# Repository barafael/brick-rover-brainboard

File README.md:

# brick-rover-brainboard
A PCB module with stm32f411 "Black Pill" and hc-12 that can serve as basic hobby RC-like sender or receiver.

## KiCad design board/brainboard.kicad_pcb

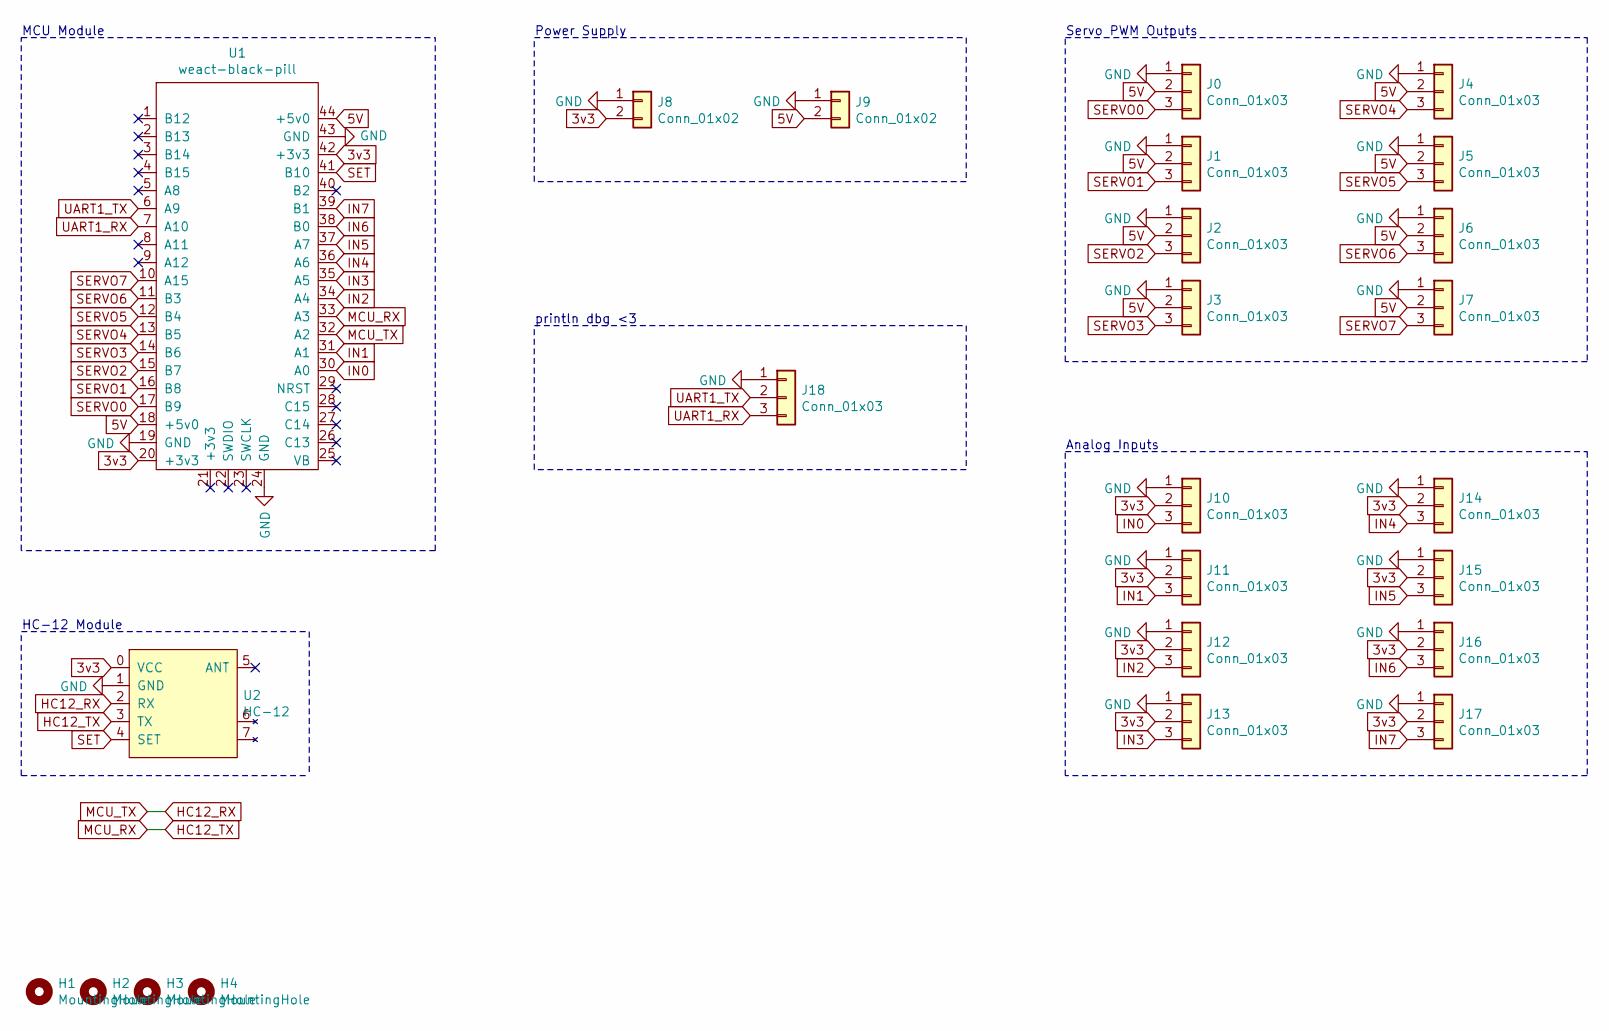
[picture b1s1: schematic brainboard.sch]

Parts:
H1: MountingHole; weact-blackpill-nodebug
H2, H3, H4: MountingHole; MountingHole_3.2mm_M3
J0, J1, J2, J3, J4, J5, J6, J7, J10, J11, J12, J13, J14, J15, J16, J17: Conn_01x03; PinHeader_1x03_P2.54mm_Vertical
J8, J9: Conn_01x02; PinHeader_1x02_P2.54mm_Vertical
J18: Conn_01x03; PinSocket_1x03_P2.54mm_Vertical
U1: weact-black-pill; weact-blackpill
U2: HC-12; hc12-module

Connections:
3v3: J8.2, J10.2, J11.2, J12.2, J13.2, J14.2, J15.2, J16.2, J17.2, U1.20 (+3v3), U1.42 (+3v3), U2.0 (VCC)
5V: J0.2, J1.2, J2.2, J3.2, J4.2, J5.2, J6.2, J7.2, J9.2, U1.18 (+5v0), U1.44 (+5v0)
GND: J0.1, J1.1, J2.1, J3.1, J4.1, J5.1, J6.1, J7.1, J8.1, J9.1, J10.1, J11.1, J12.1, J13.1, J14.1, J15.1, J16.1, J17.1, J18.1, U1.19 (GND), U1.24 (GND), U1.43 (GND), U2.1 (GND)
HC12_RX: U1.32 (A2), U2.2 (RX)
HC12_TX: U1.33 (A3), U2.3 (TX)
IN0: J10.3, U1.30 (A0)
IN1: J11.3, U1.31 (A1)
IN2: J12.3, U1.34 (A4)
IN3: J13.3, U1.35 (A5)
IN4: J14.3, U1.36 (A6)
IN5: J15.3, U1.37 (A7)
IN6: J16.3, U1.38 (B0)
IN7: J17.3, U1.39 (B1)
SERVO0: J0.3, U1.17 (B9)
SERVO1: J1.3, U1.16 (B8)
SERVO2: J2.3, U1.15 (B7)
SERVO3: J3.3, U1.14 (B6)
SERVO4: J4.3, U1.13 (B5)
SERVO5: J5.3, U1.12 (B4)
SERVO6: J6.3, U1.11 (B3)
SERVO7: J7.3, U1.10 (A15)
SET: U1.41 (B10), U2.4 (SET)
UART1_RX: J18.3, U1.7 (A10)
UART1_TX: J18.2, U1.6 (A9)

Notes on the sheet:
Analog Inputs
HC-12 Module
MCU Module
Servo PWM Outputs
Power Supply
println dbg <3

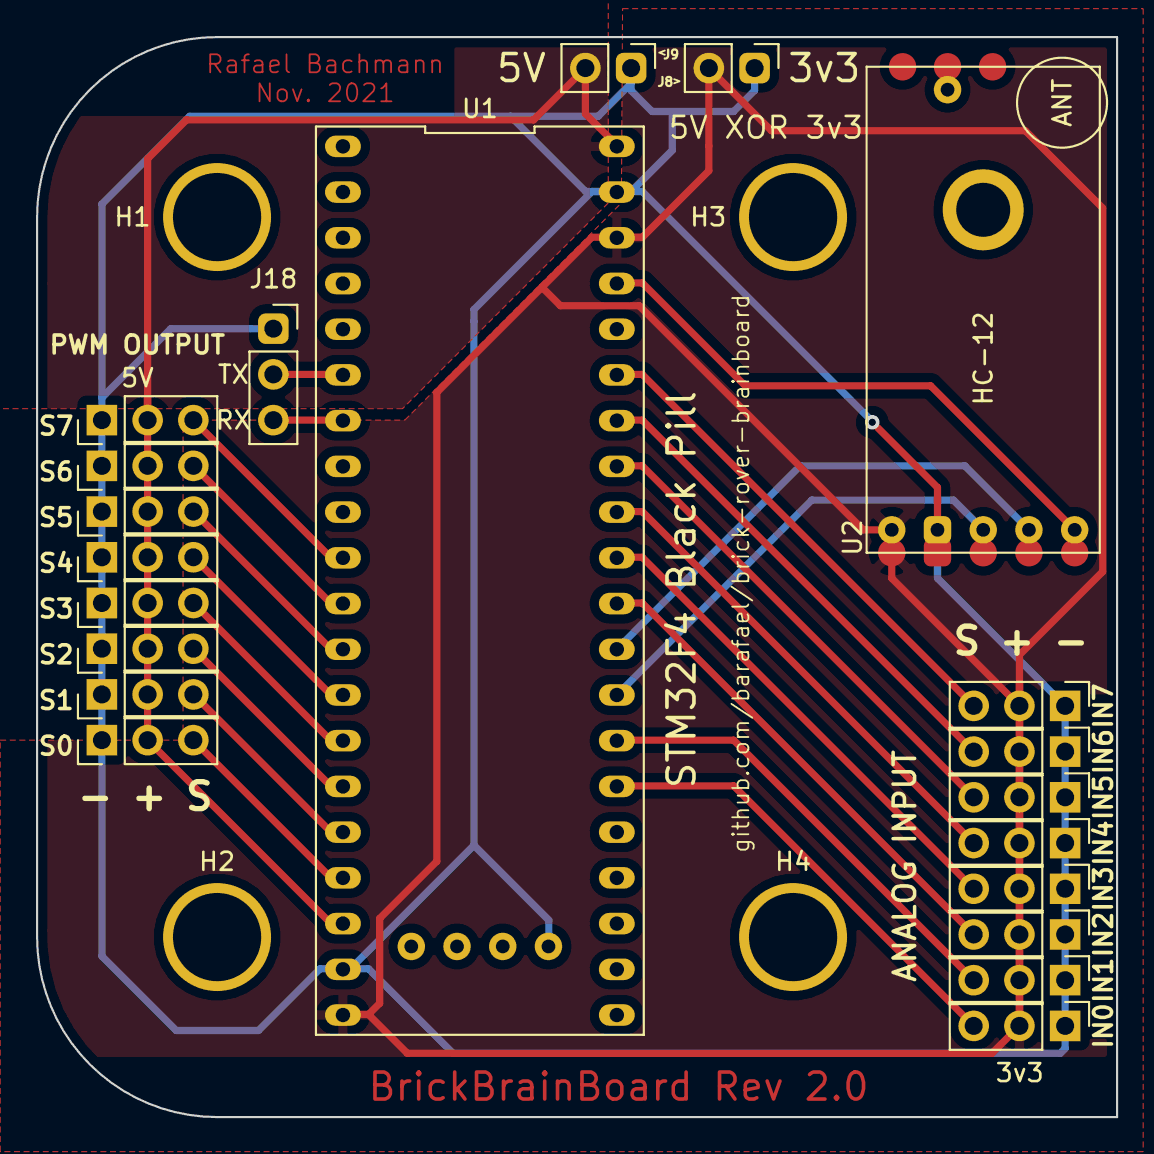
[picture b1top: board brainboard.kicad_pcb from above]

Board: 2 copper layers, 60.0 x 60.0 mm, 25 parts (0 on the bottom side), 24 nets.

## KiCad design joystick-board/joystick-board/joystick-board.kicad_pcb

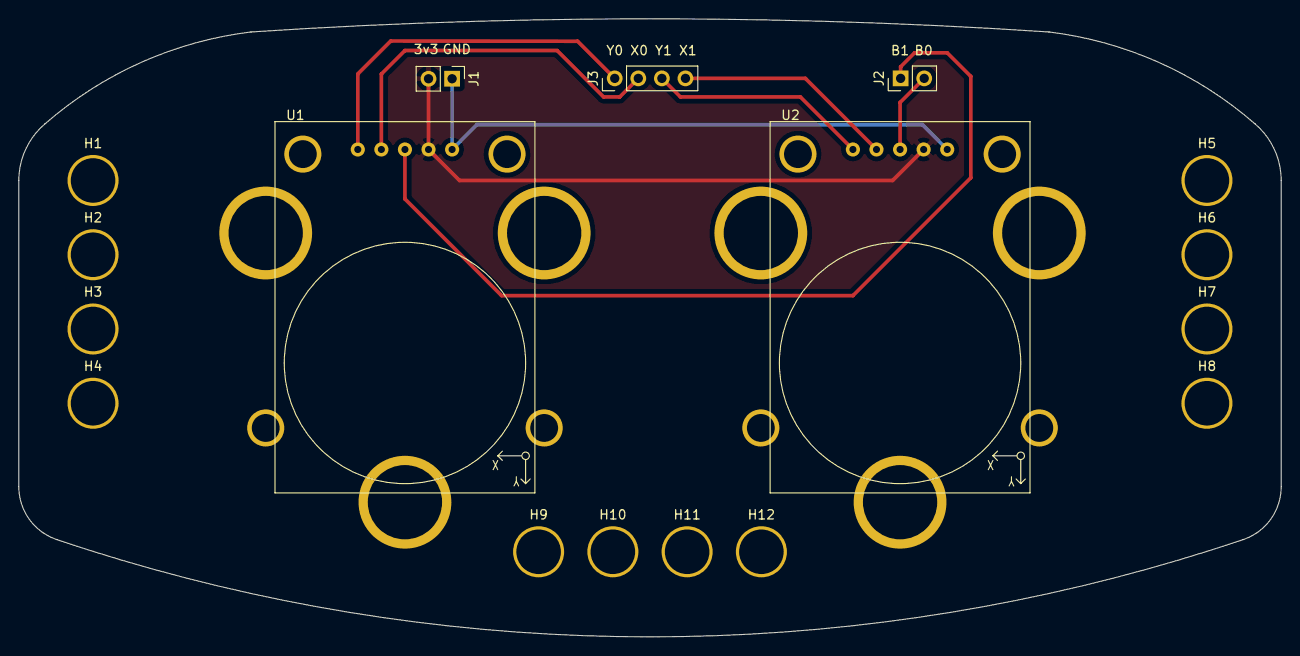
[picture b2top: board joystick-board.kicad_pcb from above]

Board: 2 copper layers, 136.0 x 66.6 mm, 17 parts (0 on the bottom side), 8 nets.

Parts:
H1, H2, H3, H4, H5, H6, H7, H8, H9, H10, H11, H12: MountingHole; MountingHole_4mm
J1, J2: Conn_01x02; PinHeader_1x02_P2.54mm_Vertical
J3: Conn_01x04; PinHeader_1x04_P2.54mm_Vertical
U1, U2: joystick

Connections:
3v3: J1.2, U1.3, U2.3
Button0: J2.1, U1.2
Button1: J2.2, U2.2
GND: J1.1, U1.4, U2.4
X0: J3.2, U1.1
X1: J3.4, U2.1
Y0: J3.1, U1.0
Y1: J3.3, U2.0

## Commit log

2021-11-01 Add analog input module
2021-11-16 Board rev. 2.0
